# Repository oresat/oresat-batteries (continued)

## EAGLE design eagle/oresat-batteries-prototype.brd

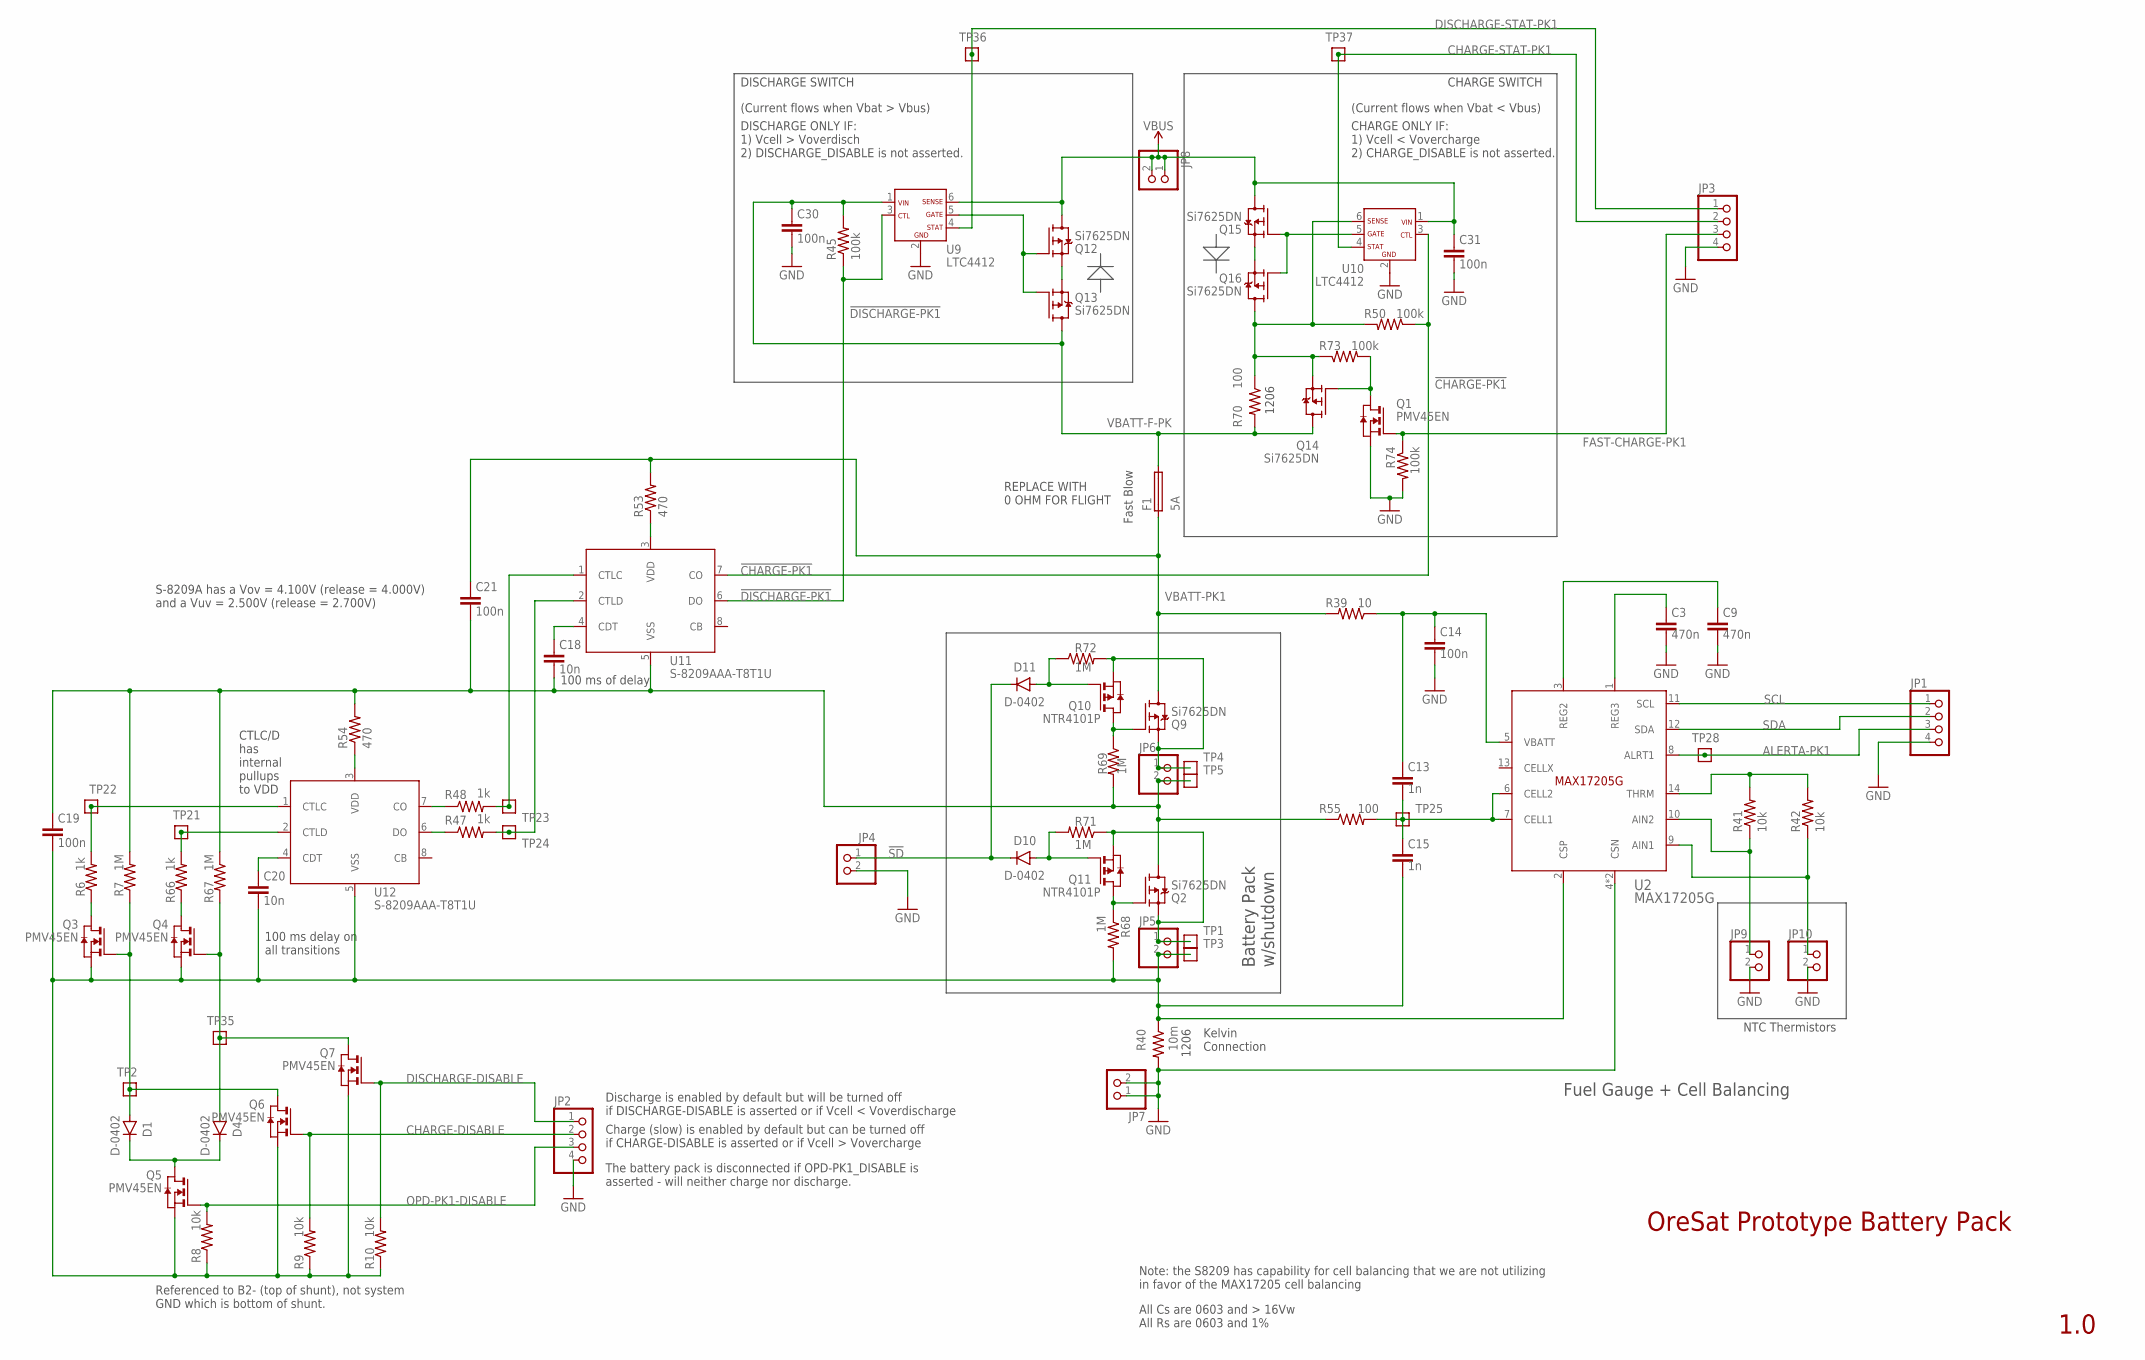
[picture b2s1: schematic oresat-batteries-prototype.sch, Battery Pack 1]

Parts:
C3, C9: 470n; .0603-C-NOSILK
C13, C15: 1n; .0603-C-NOSILK
C14, C19, C21, C30, C31: 100n; .0603-C-NOSILK
C18, C20: 10n; .0603-C-NOSILK
D1, D4, D10, D11: D-0402; .0402-B-NOSILK-DIODE; MPN 1N4148WL2-TP
F1: 5A; C0603; MPN ERB-RE5R00V
JP1, JP2, JP3: PINHD-1X4; 1X04
JP4, JP5, JP6, JP7, JP8, JP9, JP10: PINHD-1X2; 1X02
Q1, Q3, Q4, Q5, Q6, Q7: PMV45EN; SOT23; MPN DMG2302UK-7
Q2, Q9, Q12, Q13, Q14, Q15, Q16: Si7625DN; POWERPAK-1212-8; MPN SI7625DN-T1-GE3
Q10, Q11: NTR4101P; SOT23; MPN DMG3401LSN-7
R6, R47, R48, R66: 1k; .0603-C-NOSILK
R7, R67, R68, R69, R71, R72: 1M; .0603-C-NOSILK
R8, R9, R10, R41, R42: 10k; .0603-C-NOSILK
R39: 10; .0603-C-NOSILK
R40: 10m; 1206-C
R45, R50, R73, R74: 100k; .0603-C-NOSILK
R53, R54: 470; .0603-C-NOSILK
R55: 100; .0603-C-NOSILK
R70: 100; 1206-C
TP1, TP2, TP3, TP4, TP5, TP21, TP22, TP23, TP24, TP25, TP28, TP35, TP36, TP37: TEST-POINT; 2MM-TEST-POINT
U2: MAX17205G; 21-0137I_T1433-2; MPN MAX17205G+T
U9, U10: LTC4412; SOT23-6; MPN LTC4412HS6#TRMPBF
U11, U12: S-8209AAA-T8T1U; TSSOP8; MPN S-8209AAA-T8T1U

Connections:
!CHARGE-PK1: R50.1, U10.3 (CTL), U11.7 (CO)
!DISCHARGE-PK1: R45.1, U9.3 (CTL), U11.6 (DO)
!FAST-CHARGE-PK1: Q1.3 (D), Q14.4 (G), R73.2
!SD: D10.C, D11.C, JP4.1
AIN1-PK1: JP10.1, R42.1, U2.9 (AIN1)
AIN2-PK1: JP9.1, R41.1, U2.10 (AIN2)
ALERTA-PK1: JP1.3, TP28.1, U2.8 (ALRT1)
CELL1-PK1: C13.2, C15.1, R55.2, TP25.1, U2.6 (CELL2), U2.7 (CELL1)
CHARGE-DISABLE: JP2.2, Q6.1 (G), R9.2
CHARGE-STAT-PK1: JP3.2, TP37.1, U10.4 (STAT)
CSP-PK1: C15.2, C19.2, C20.2, JP5.2, Q3.2 (S), Q4.2 (S), Q5.2 (S), Q6.2 (S), Q7.2 (S), R8.1, R9.1, R10.1, R40.1, R68.2, TP3.1, U2.2 (CSP), U12.5 (VSS)
DISCHARGE-DISABLE: JP2.1, Q7.1 (G), R10.2
DISCHARGE-STAT-PK1: JP3.1, TP36.1, U9.4 (STAT)
FAST-CHARGE-PK1: JP3.3, Q1.1 (G), R74.1
GND: C3.2, C9.2, C14.2, C30.2, C31.2, JP1.4, JP2.4, JP3.4, JP4.2, JP7.1, JP7.2, JP9.2, JP10.2, Q1.2 (S), R40.2, R74.2, U2.4 (CSN), U2.EP (CSN), U9.2 (GND), U10.2 (GND)
unnamed: D1.C, D4.C, Q5.3 (D)
unnamed: R47.2, TP24.1, U11.2 (CTLD)
unnamed: R47.1, U12.6 (DO)
unnamed: R48.2, TP23.1, U11.1 (CTLC)
unnamed: Q4.3 (D), R66.1
unnamed: R48.1, U12.7 (CO)
unnamed: C20.1, U12.4 (CDT)
unnamed: Q12.4 (G), Q13.4 (G), U9.5 (GATE)
unnamed: Q12.1 (S), Q12.2 (S), Q12.3 (S), Q13.1 (S), Q13.2 (S), Q13.3 (S)
unnamed: Q3.3 (D), R6.1
unnamed: D4.A, Q4.1 (G), Q7.3 (D), R67.2, TP35.1
unnamed: C18.1, U11.4 (CDT)
unnamed: R6.2, TP22.1, U12.1 (CTLC)
unnamed: Q9.4 (G), Q10.3 (D), R69.1
unnamed: R53.1, U11.3 (VDD)
unnamed: R54.1, U12.3 (VDD)
unnamed: R66.2, TP21.1, U12.2 (CTLD)
unnamed: D10.A, Q11.1 (G), R71.2
unnamed: Q14.1 (S), Q14.2 (S), Q14.3 (S), Q16.5 (D), Q16.6 (D), Q16.7 (D), Q16.8 (D), Q16.PAD (D), R50.2, R70.1, R73.1, U10.6 (SENSE)
unnamed: JP6.1, Q9.1 (S), Q9.2 (S), Q9.3 (S), Q10.2 (S), R72.2, TP4.1
unnamed: Q15.4 (G), Q16.4 (G), U10.5 (GATE)
unnamed: Q15.1 (S), Q15.2 (S), Q15.3 (S), Q16.1 (S), Q16.2 (S), Q16.3 (S)
unnamed: Q2.4 (G), Q11.3 (D), R68.1
unnamed: D11.A, Q10.1 (G), R72.1
unnamed: D1.A, Q3.1 (G), Q6.3 (D), R7.1, TP2.1
unnamed: JP5.1, Q2.1 (S), Q2.2 (S), Q2.3 (S), Q11.2 (S), R71.1, TP1.1
unnamed: C18.2, C19.1, C21.2, JP6.2, Q2.5 (D), Q2.6 (D), Q2.7 (D), Q2.8 (D), Q2.PAD (D), R7.2, R54.2, R55.1, R67.1, R69.2, TP5.1, U11.5 (VSS)
OPD-PK1-DISABLE: JP2.3, Q5.1 (G), R8.2
REG2-PK1: C9.1, U2.3 (REG2)
REG3-PK1: C3.1, U2.1 (REG3)
SCL: JP1.1, U2.11 (SCL)
SDA: JP1.2, U2.12 (SDA)
THRM-PK1: R41.2, R42.2, U2.14 (THRM)
VBATT-F-PK: C30.1, F1.2, Q13.5 (D), Q13.6 (D), Q13.7 (D), Q13.8 (D), Q13.PAD (D), Q14.5 (D), Q14.6 (D), Q14.7 (D), Q14.8 (D), Q14.PAD (D), R45.2, R70.2, U9.1 (VIN)
VBATT-PK1: C21.1, F1.1, Q9.5 (D), Q9.6 (D), Q9.7 (D), Q9.8 (D), Q9.PAD (D), R39.2, R53.2
VBATT-PL1: C13.1, C14.1, R39.1, U2.5 (VBATT)
VBUS: C31.1, JP8.1, JP8.2, Q12.5 (D), Q12.6 (D), Q12.7 (D), Q12.8 (D), Q12.PAD (D), Q15.5 (D), Q15.6 (D), Q15.7 (D), Q15.8 (D), Q15.PAD (D), U9.6 (SENSE), U10.1 (VIN)

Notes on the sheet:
1206
NTC Thermistors
Battery Pack w/shutdown
Fuel Gauge + Cell Balancing
Note: the S8209 has capability for cell balancing that we are not utilizing in favor of the MAX17205 cell balancing
100 ms of delay
Fast Blow
DISCHARGE SWITCH
REPLACE WITH 0 OHM FOR FLIGHT
(Current flows when Vbat > Vbus)
DISCHARGE ONLY IF: 1) Vcell > Voverdisch 2) DISCHARGE_DISABLE is not asserted.
CTLC/D has internal pullups to VDD
100 ms delay on all transitions
Discharge is enabled by default but will be turned off if DISCHARGE-DISABLE is asserted or if Vcell < Voverdischarge
Charge (slow) is enabled by default but can be turned off if CHARGE-DISABLE is asserted or if Vcell > Vovercharge
CHARGE SWITCH
(Current flows when Vbat < Vbus)
CHARGE ONLY IF: 1) Vcell < Vovercharge 2) CHARGE_DISABLE is not asserted.
OreSat Prototype Battery Pack
1.0
Kelvin Connection
S-8209A has a Vov = 4.100V (release = 4.000V) and a Vuv = 2.500V (release = 2.700V)
Referenced to B2- (top of shunt), not system GND which is bottom of shunt.
The battery pack is disconnected if OPD-PK1_DISABLE is asserted - will neither charge nor discharge.
All Cs are 0603 and > 16Vw All Rs are 0603 and 1%

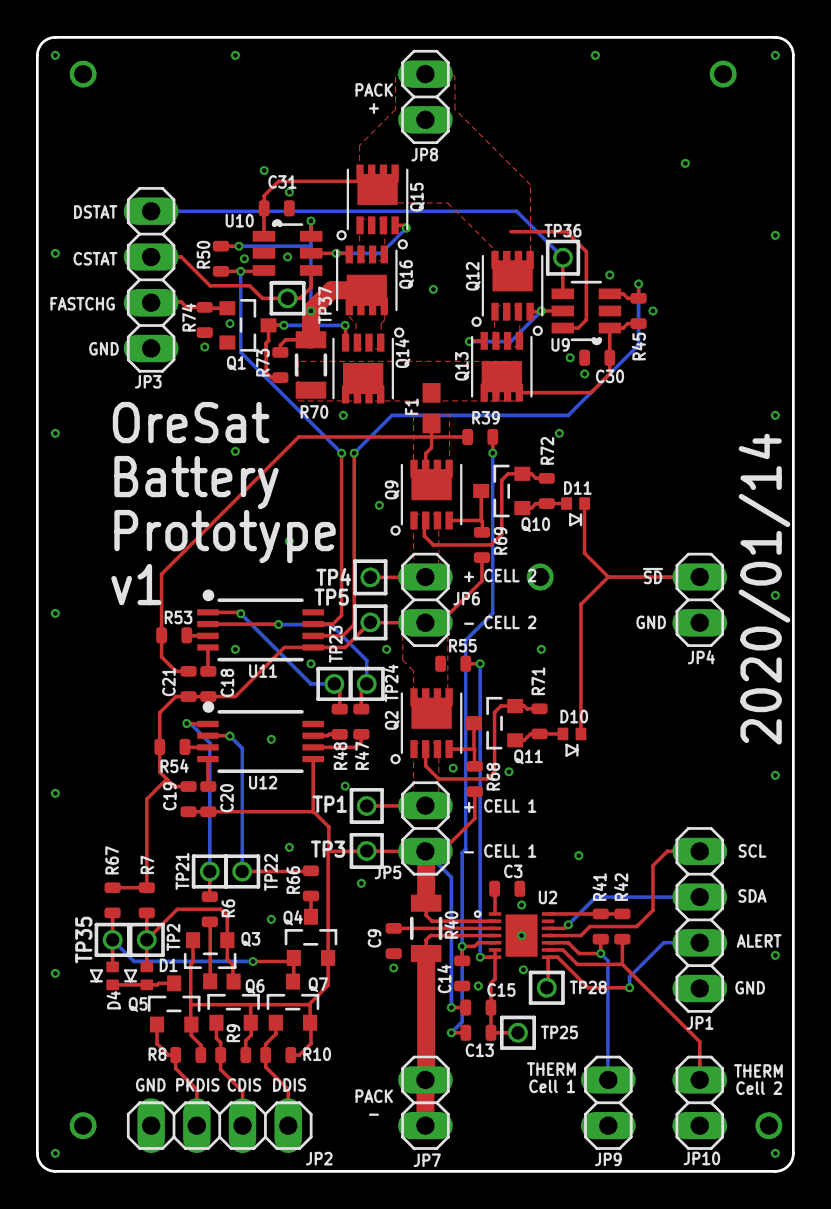
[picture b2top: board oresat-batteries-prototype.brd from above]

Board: 2 copper layers, 42.0 x 63.0 mm, 85 parts (0 on the bottom side), 52 nets.

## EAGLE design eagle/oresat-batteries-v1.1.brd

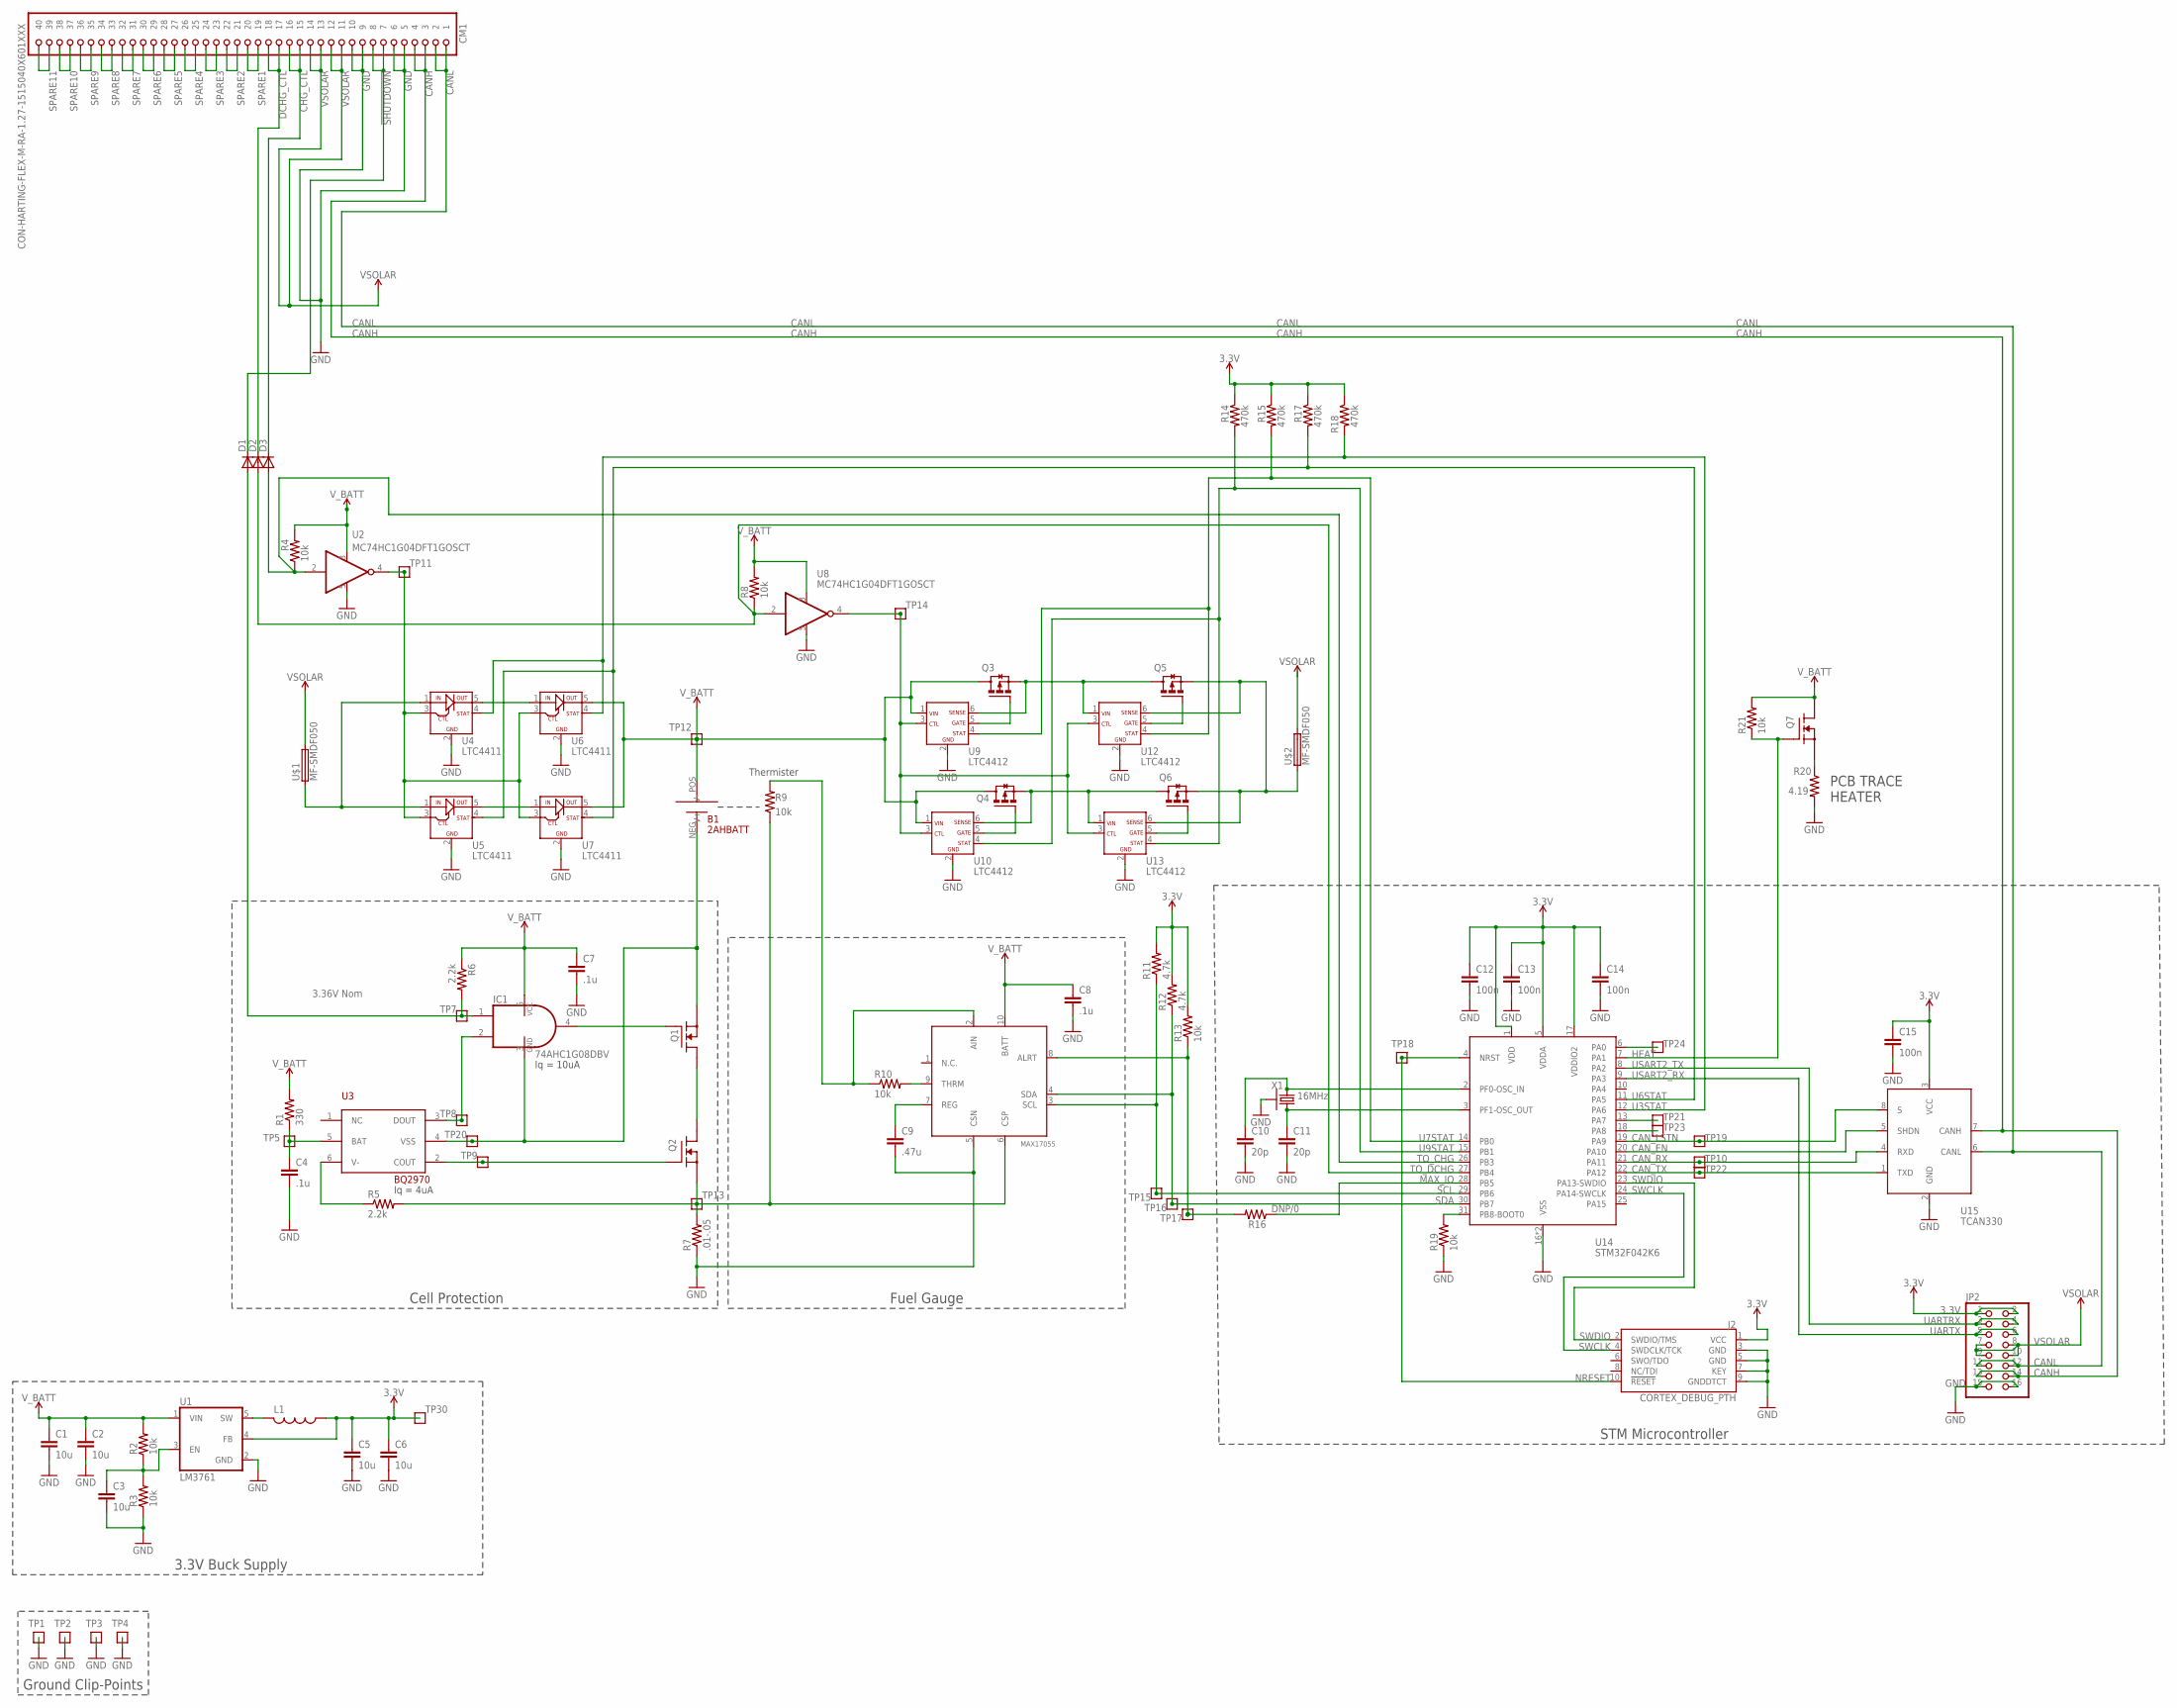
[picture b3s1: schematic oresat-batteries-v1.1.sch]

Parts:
B1: 2AHBATT; 2AH_605060
C1, C2, C3, C5, C6: 10u; C0805
C4, C7, C8: .1u; C0603
C9: .47u; C0603
C10, C11: 20p; C0603
C12, C13, C14, C15: 100n; C0603
CM1: CON-HARTING-FLEX-M-RA-1.27-1515040X601XXX; CON-1.27-M-RA-HARTING-1515040X601XXX
D1, D2, D3: CMDD6001; SOD323
IC1: 74AHC1G08DBV; SOT23-5
J2: CORTEX_DEBUG_PTH; 2X5-PTH-1.27MM
JP2: PINHD-2X8; 2X08
L1: L-USL2012C; L2012C
Q1, Q2, Q7: CSD16340Q3; Q3
Q3, Q4, Q5, Q6: TPN4R712MD; TSON-ADVANCE-3X3
R1: 330; R0603
R2, R3, R4, R8, R9, R10, R13, R19, R21: 10k; R0603
R5, R6: 2.2k; R0603
R7: .01-.05; R2512
R11, R12: 4.7k; R0603
R14, R15, R17, R18: 470k; R0603
R16: DNP/0; R0603
R20: 4.19; RES_HEATER
TP1, TP2, TP3, TP4, TP5, TP7, TP8, TP9, TP10, TP11, TP12, TP13, TP14, TP15, TP16, TP17, TP18, TP19, TP20, TP21, TP22, TP23, TP24, TP30: TP; 2MM_TP
U1: LM3761; SOT23-5
U2, U8: MC74HC1G04DFT1GOSCT; SC70-5
U3: BQ2970; PSOP6
U4, U5, U6, U7: LTC4411; SOT23-5-B
U9, U10, U12, U13: LTC4412; SOT23-6
U11: MAX17055; TDFN-10L
U14: STM32F042K6; QFP32-7X7
U15: TCAN330; SOT23-8_TI-DCN
U$1, U$2: MF-SMDF050
X1: 16MHz; CRYSTAL_2.5X2

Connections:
3.3V: C5.1, C6.1, C12.1, C13.1, C14.1, C15.1, J2.1 (VCC), JP2.1, JP2.2, L1.1, R11.2, R12.2, R13.2, R14.1, R15.1, R17.1, R18.1, TP30.P$1, U1.4 (FB), U14.1 (VDD), U14.5 (VDDA), U14.17 (VDDIO2), U15.3 (VCC)
4411MB: U5.5 (OUT), U7.1 (IN)
4411_MT: U4.5 (OUT), U6.1 (IN)
!SHUTDOWN: CM1.7, CM1.8, D1.1 (C)
ALERT: R13.1, R16.2, TP17.P$1, U11.8 (ALRT)
ANDDRIVE: IC1.4 (O), Q1.P$4 (G)
BATT-: B1.NEG (V-), IC1.3 (GND), Q1.P$1 (S), Q1.P$2 (S), Q1.P$3 (S), TP20.P$1, U3.4 (VSS)
BETSHUT: Q1.P$5 (D), Q1.P$6 (D), Q1.P$7 (D), Q1.P$8 (D), Q1.P$9 (D), Q2.P$5 (D), Q2.P$6 (D), Q2.P$7 (D), Q2.P$8 (D), Q2.P$9 (D)
BGDOUT: IC1.2 (I1), TP8.P$1, U3.3 (DOUT)
BQBAT: C4.1, R1.1, TP5.P$1, U3.5 (BAT)
BQCOUT: Q2.P$4 (G), TP9.P$1, U3.2 (COUT)
BQVMIN: R5.1, U3.6 (V-)
CANH: CM1.3, CM1.4, JP2.13, JP2.14, U15.7 (CANH)
CANL: CM1.1, CM1.2, JP2.11, JP2.12, U15.6 (CANL)
CAN_EN: U14.20 (PA10), U15.5 (SHDN)
CAN_LSTN: TP19.P$1, U14.19 (PA9), U15.8 (S)
CAN_RX: TP10.P$1, U14.21 (PA11), U15.4 (RXD)
CAN_TX: TP22.P$1, U14.22 (PA12), U15.1 (TXD)
CHG_CTL: CM1.15, CM1.16, D3.1 (C)
CHG_SHD: TP11.P$1, U2.4 (OUT), U4.3 (CTL), U5.3 (CTL), U6.3 (CTL), U7.3 (CTL)
C_SENSE: Q2.P$1 (S), Q2.P$2 (S), Q2.P$3 (S), R5.2, R7.2, R9.1, TP13.P$1, U11.6 (CSP)
DCHG_CTL: CM1.17, CM1.18, D2.1 (C)
DSCHG_SHD: TP14.P$1, U8.4 (OUT), U9.3 (CTL), U10.3 (CTL), U12.3 (CTL), U13.3 (CTL)
GND: C1.2, C2.2, C3.2, C4.2, C5.2, C6.2, C7.2, C8.2, C9.2, C10.2, C11.2, C12.2, C13.2, C14.2, C15.2, CM1.5, CM1.6, CM1.9, CM1.10, J2.3 (GND), J2.5 (GND), J2.7 (KEY), J2.9 (GNDDTCT), JP2.15, JP2.16, R3.1, R7.1, R19.1, R20.V- (2), TP1.P$1, TP2.P$1, TP3.P$1, TP4.P$1, U1.2 (GND), U2.5 (GND), U4.2 (GND), U5.2 (GND), U6.2 (GND), U7.2 (GND), U8.5 (GND), U9.2 (GND), U10.2 (GND), U11.5 (CSN), U12.2 (GND), U13.2 (GND), U14.16 (VSS), U14.32 (VSS), U15.2 (GND), X1.2 (SHIELD), X1.4 (SHIELD)
HEAT: Q7.P$4 (G), R21.1, U14.7 (PA1)
INFUSE: U4.1 (IN), U5.1 (IN), U$1.1
MAX_IO: R16.1, U14.28 (PB5)
unnamed: L1.2, U1.5 (SW)
unnamed: R19.2, U14.31 (PB8-BOOT0)
unnamed: TP23.P$1, U14.18 (PA8)
unnamed: C3.1, R2.1, R3.2, U1.3 (EN)
unnamed: Q5.4 (G), U12.5 (GATE)
unnamed: Q3.1 (S), Q3.2 (S), Q3.3 (S), Q5.5 (D), Q5.6 (D), Q5.7 (D), Q5.8 (D), U9.6 (SENSE), U12.1 (VIN)
unnamed: Q3.4 (G), U9.5 (GATE)
unnamed: Q7.P$1 (S), Q7.P$2 (S), Q7.P$3 (S), R20.V+ (1)
unnamed: TP24.P$1, U14.6 (PA0)
unnamed: Q6.4 (G), U13.5 (GATE)
unnamed: Q4.1 (S), Q4.2 (S), Q4.3 (S), Q6.5 (D), Q6.6 (D), Q6.7 (D), Q6.8 (D), U10.6 (SENSE), U13.1 (VIN)
unnamed: Q4.4 (G), U10.5 (GATE)
NRESET: J2.10 (!RESET), TP18.P$1, U14.4 (NRST)
OSC_IN: C10.1, U14.2 (PF0-OSC_IN), X1.1
OSC_OUT: C11.1, U14.3 (PF1-OSC_OUT), X1.3 (2)
OUTFUSE: Q5.1 (S), Q5.2 (S), Q5.3 (S), Q6.1 (S), Q6.2 (S), Q6.3 (S), U12.6 (SENSE), U13.6 (SENSE), U$2.1
REG: C9.1, U11.7 (REG)
SCL: R11.1, TP15.P$1, U11.3 (SCL), U14.29 (PB6)
SDA: R12.1, TP16.P$1, U11.4 (SDA), U14.30 (PB7)
SPARE1: CM1.19, CM1.20
SPARE2: CM1.21, CM1.22
SPARE3: CM1.23, CM1.24
SPARE4: CM1.25, CM1.26
SPARE5: CM1.27, CM1.28
SPARE6: CM1.29, CM1.30
SPARE7: CM1.31, CM1.32
SPARE8: CM1.33, CM1.34
SPARE9: CM1.35, CM1.36
SPARE10: CM1.37, CM1.38
SPARE11: CM1.39, CM1.40
SWCLK: J2.4 (SWDCLK/TCK), U14.24 (PA14-SWCLK)
SWDIO: J2.2 (SWDIO/TMS), U14.23 (PA13-SWDIO)
SYSSHD: D1.2 (A), IC1.1 (I0), R6.2, TP7.P$1
TEMPSENSE: R9.2, R10.1, U11.2 (AIN)
THRM: R10.2, U11.9 (THRM)
TO_CHG: D3.2 (A), R4.1, U2.2 (INA), U14.26 (PB3)
TO_DCHG: D2.2 (A), R8.1, U8.2 (INA), U14.27 (PB4)
TP21: TP21.P$1, U14.13 (PA7)
U3STAT: R18.2, U4.4 (STAT), U6.4 (STAT), U14.12 (PA6)
U6STAT: R17.2, U5.4 (STAT), U7.4 (STAT), U14.11 (PA5)
U7STAT: R15.2, U9.4 (STAT), U12.4 (STAT), U14.14 (PB0)
U9STAT: R14.2, U10.4 (STAT), U13.4 (STAT), U14.15 (PB1)
USART2_RX: JP2.5, JP2.6, U14.9 (PA3)
USART2_TX: JP2.3, JP2.4, U14.8 (PA2)
VSOLAR: CM1.11, CM1.12, CM1.13, CM1.14, JP2.7, JP2.8, JP2.9, JP2.10, U$1.2, U$2.2
V_BATT: B1.POS (V+), C1.1, C2.1, C7.1, C8.1, IC1.5 (VCC), Q3.5 (D), Q3.6 (D), Q3.7 (D), Q3.8 (D), Q4.5 (D), Q4.6 (D), Q4.7 (D), Q4.8 (D), Q7.P$5 (D), Q7.P$6 (D), Q7.P$7 (D), Q7.P$8 (D), Q7.P$9 (D), R1.2, R2.2, R4.2, R6.1, R8.2, R21.2, TP12.P$1, U1.1 (VIN), U2.3 (VCC), U6.5 (OUT), U7.5 (OUT), U8.3 (VCC), U9.1 (VIN), U10.1 (VIN), U11.10 (BATT)

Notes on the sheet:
SCL
SDA
USART2_TX
USART2_RX
CAN_LSTN
CAN_EN
CAN_RX
CAN_TX
SWDIO
SWCLK
UARTRX
UARTX
CANH
VSOLAR
CANL
GND
HEAT
3.36V Nom
Fuel Gauge
STM Microcontroller
Cell Protection
Thermister
Iq = 10uA
Iq = 4uA
PCB TRACE HEATER
3.3V Buck Supply
Ground Clip-Points

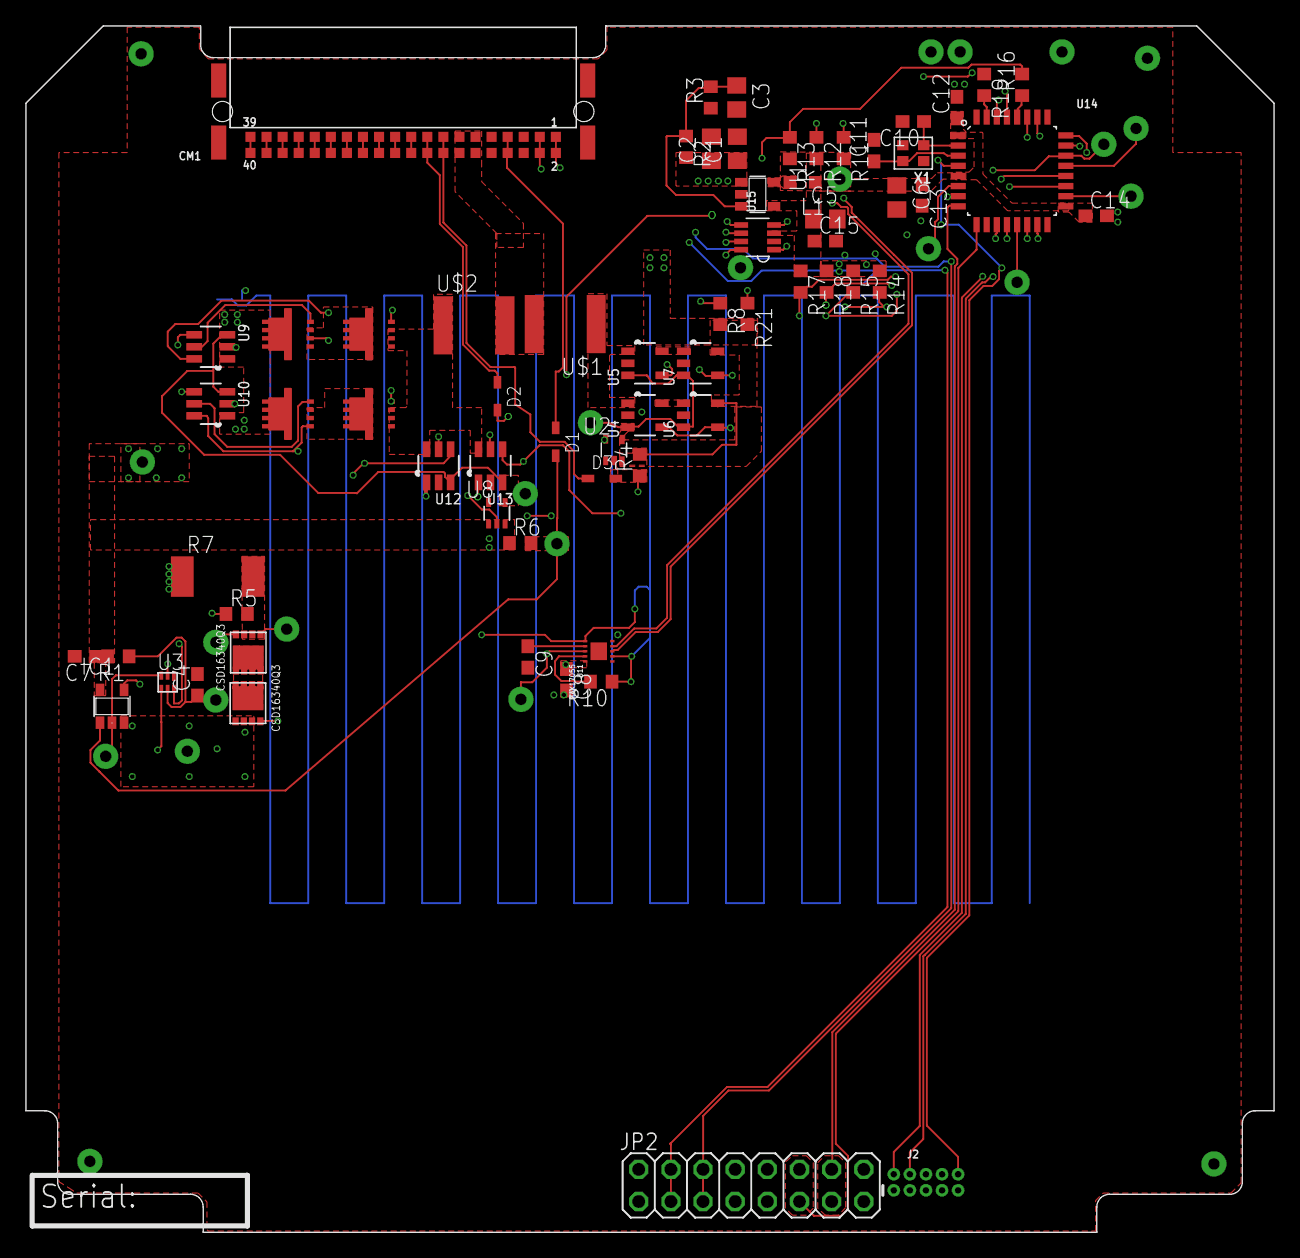
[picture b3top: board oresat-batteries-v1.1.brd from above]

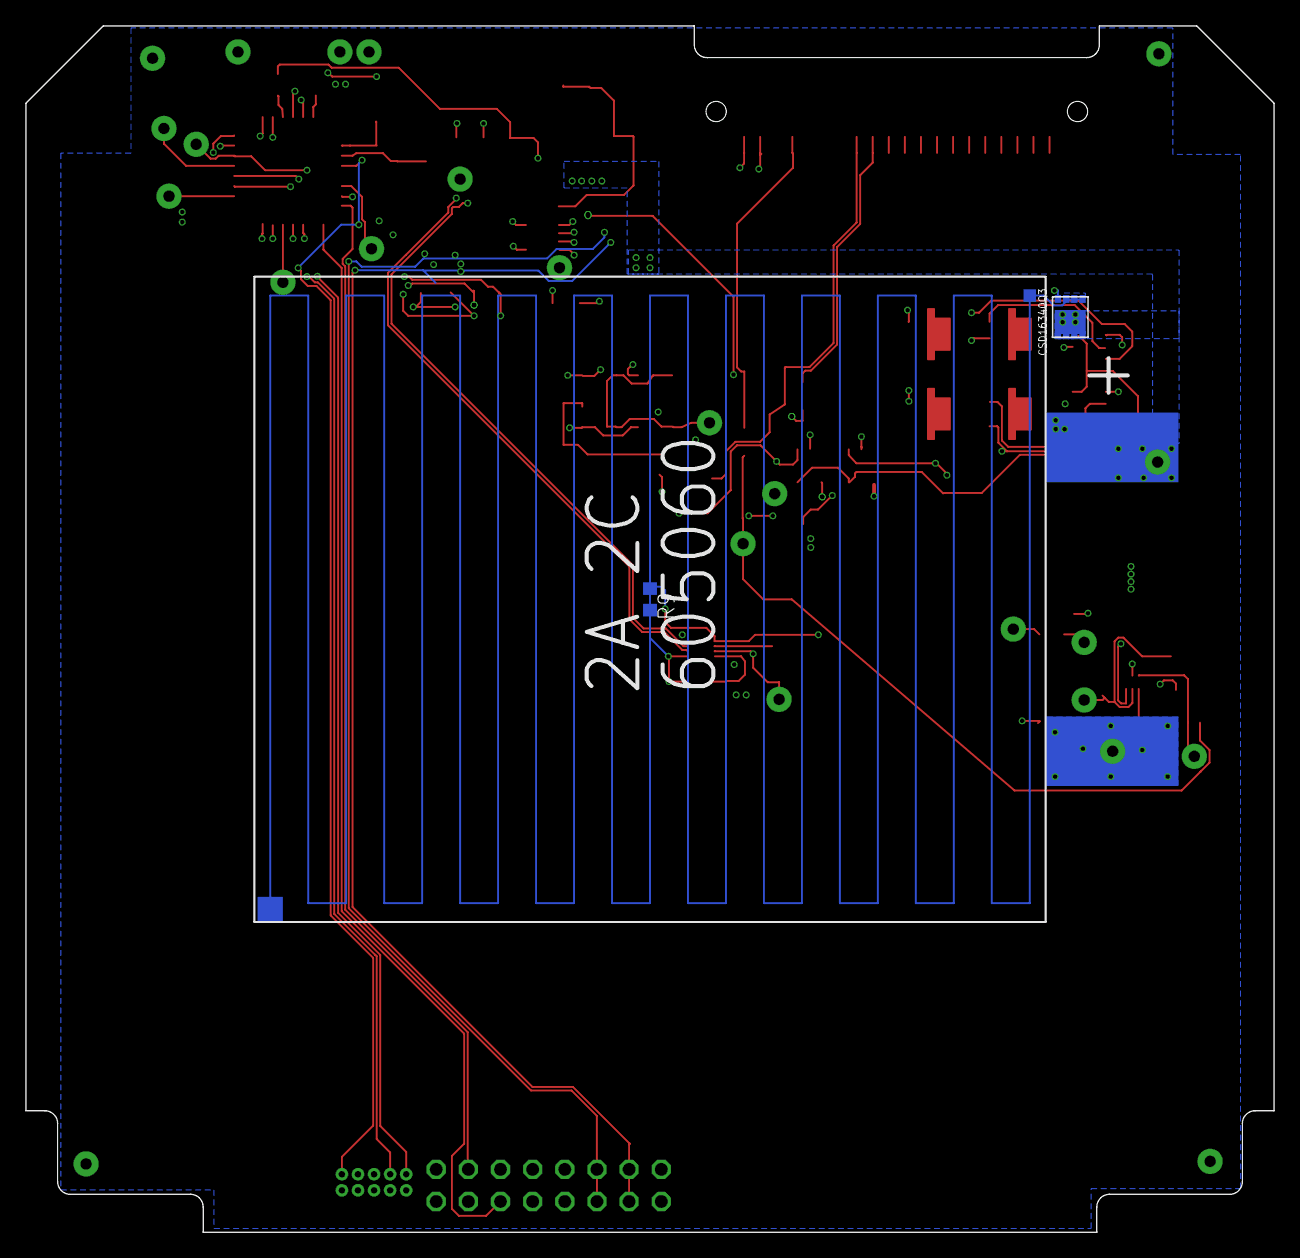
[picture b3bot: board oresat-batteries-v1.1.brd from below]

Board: 4 copper layers, 98.6 x 95.3 mm, 95 parts (4 on the bottom side), 73 nets.

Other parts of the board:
U$7: ORESAT-CARD-V0.5

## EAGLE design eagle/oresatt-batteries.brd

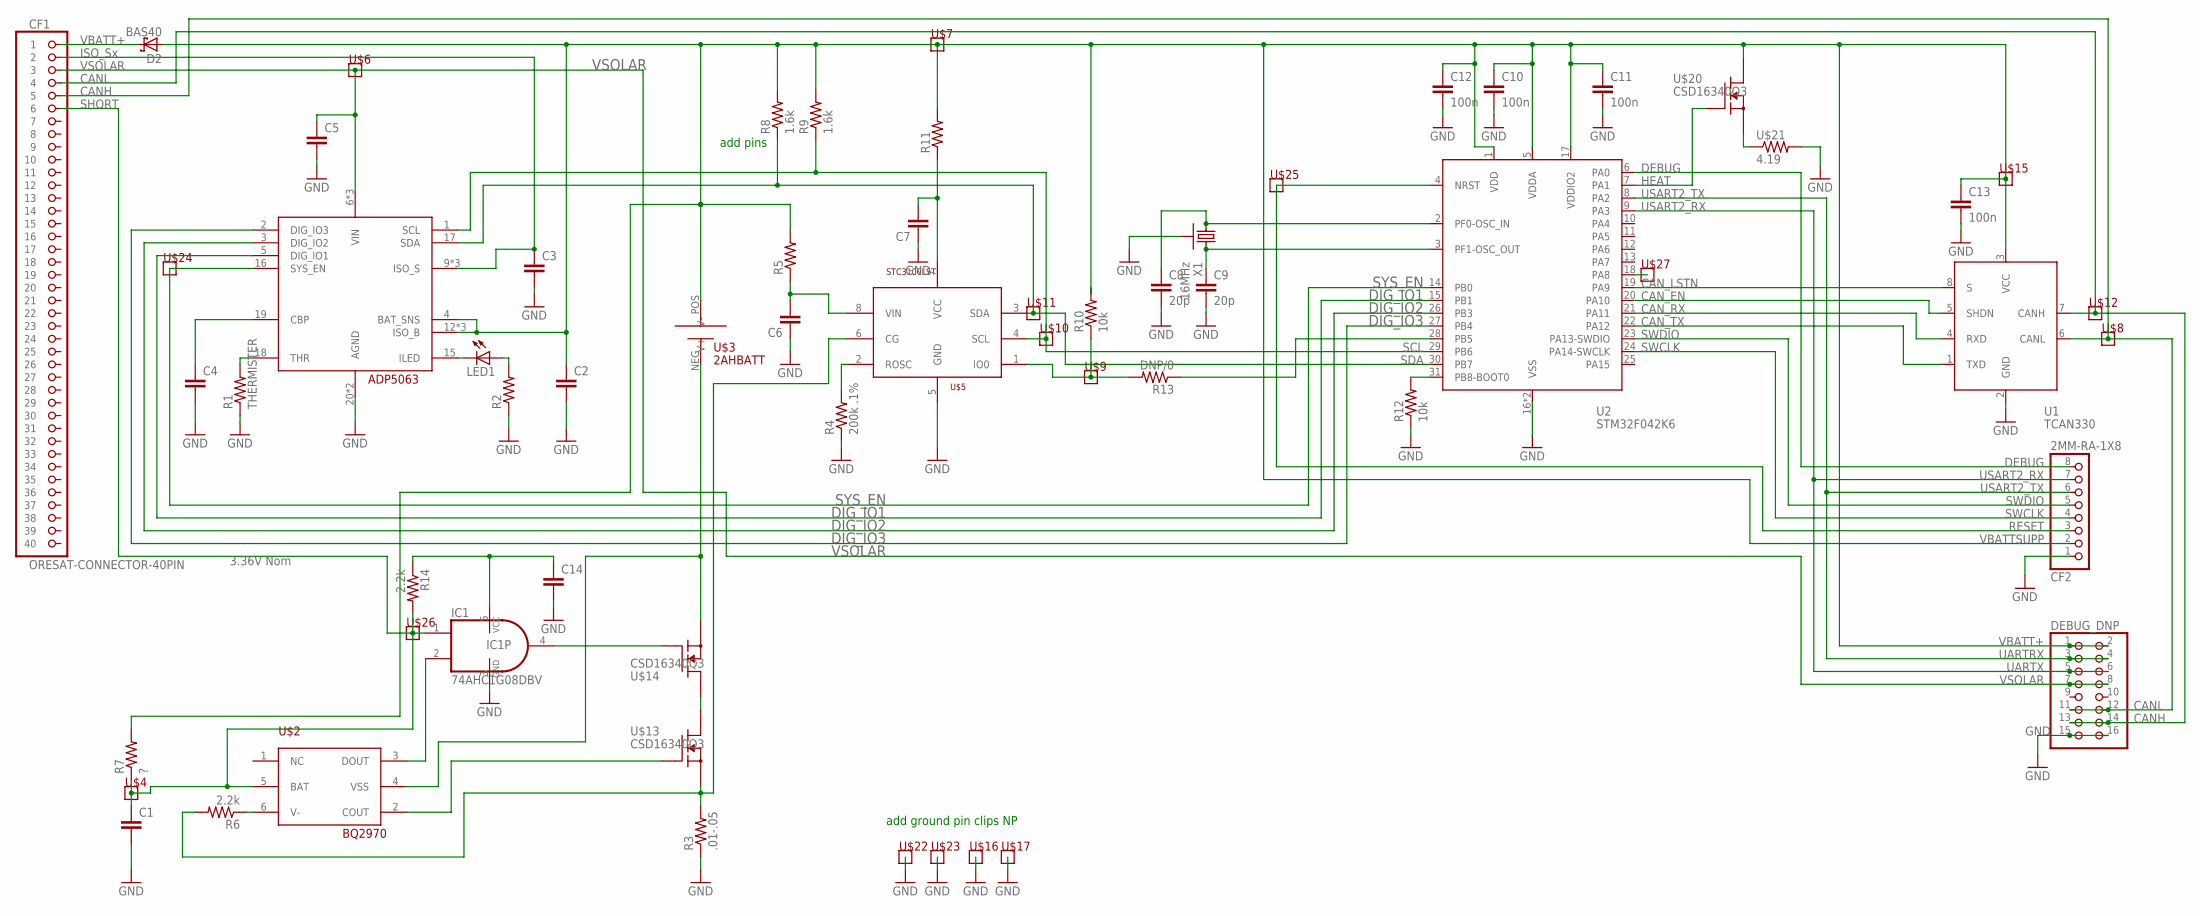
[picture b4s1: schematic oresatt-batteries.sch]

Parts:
C1, C2, C3, C4, C5, C6, C7, C14: C-EUC0603; C0603
C8, C9: 20p; C0603
C10, C11, C12, C13: 100n; C0603
CF1: ORESAT-CONNECTOR-40PIN; HARWIN-ARCHER-M50-3202045
CF2: 2MM-RA-1X8; CF-2MM-RA-1X8-PRECIDIP-831
D2: BAS40; SOT23
DEBUG_DNP: PINHD-2X8; 2X08
IC1: 74AHC1G08DBV; SOT23-5
LED1: LEDCHIPLED_0603; CHIPLED_0603
R1: THERMISTER; R0603
R2, R5, R11: R-US_R0603; R0603
R3: .01-.05; R0603
R4: 200k .1%; R0603
R6, R14: 2.2k; R0603
R7: ?; R0603
R8, R9: 1.6k; R0603
R10, R12: 10k; R0603
R13: DNP/0; R0603
U1: TCAN330; SOT23-8_TI-DCN
U2: STM32F042K6; QFP32-7X7
U$1: ADP5063; 20_4X4_VVTQ
U$2: BQ2970; PSOP6
U$3: 2AHBATT; 2AH_605060
U$4, U$6, U$7, U$8, U$9, U$10, U$11, U$12, U$15, U$16, U$17, U$22, U$23, U$24, U$25, U$26, U$27: TP; 2MM_TP
U$5: STC3100LST; MINISO-8
U$13, U$14, U$20: CSD16340Q3; Q3
U$21: 4.19; RES_HEATER
X1: 16MHz; CRYSTAL_2.5X2

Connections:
ADP_CBP: C4.1, U$1.19 (CBP)
ADP_LED: LED1.C, U$1.15 (ILED)
ADP_THR: R1.2, U$1.18 (THR)
ANDDRIVE: IC1.4 (O), U$14.P$4 (G)
BETSHUT: U$13.P$5 (D), U$13.P$6 (D), U$13.P$7 (D), U$13.P$8 (D), U$13.P$9 (D), U$14.P$5 (D), U$14.P$6 (D), U$14.P$7 (D), U$14.P$8 (D), U$14.P$9 (D)
BQBAT: C1.1, CF1.P$6 (6), IC1.1 (I0), R7.1, R14.2, U$2.5 (BAT)
BQVMIN: R6.1, U$2.6 (V-)
CANH: CF1.P$4 (4), DEBUG_DNP.13, DEBUG_DNP.14, U1.7 (CANH)
CANL: CF1.P$5 (5), DEBUG_DNP.11, DEBUG_DNP.12, U1.6 (CANL)
CAN_EN: U1.5 (SHDN), U2.20 (PA10)
CAN_LSTN: U1.8 (S), U2.19 (PA9)
CAN_RX: U1.4 (RXD), U2.21 (PA11)
CAN_TX: U1.1 (TXD), U2.22 (PA12)
COUT: U$2.2 (COUT), U$13.P$4 (G)
C_SENSE: R3.2, R6.2, U$5.6 (CG), U$13.P$1 (S), U$13.P$2 (S), U$13.P$3 (S)
DIG_IO1: U2.15 (PB1), U$1.5 (DIG_IO1)
DIG_IO2: U2.26 (PB3), U$1.3 (DIG_IO2)
DIG_IO3: U2.27 (PB4), U$1.2 (DIG_IO3)
GND: C1.2, C2.2, C3.2, C4.2, C5.2, C6.1, C7.1, C8.2, C9.2, C10.2, C11.2, C12.2, C13.2, C14.2, CF2.1, DEBUG_DNP.15, DEBUG_DNP.16, IC1.3 (GND), R1.1, R2.1, R3.1, R4.1, R12.1, U1.2 (GND), U2.16 (VSS), U2.32 (VSS), U$1.20 (AGND), U$1.P$1 (AGND), U$5.5 (GND), U$21.V- (2), X1.2 (SHIELD), X1.4 (SHIELD)
HEAT: U2.7 (PA1), U$20.P$4 (G)
IO0: R10.1, R13.2, U$5.1 (IO0)
ISO_S: C3.1, CF1.P$2 (2), U$1.9 (ISO_S), U$1.10 (ISO_S), U$1.11 (ISO_S)
LEDNP: LED1.A, R2.2
unnamed: C7.2, R11.1, U$5.7 (VCC)
unnamed: R12.2, U2.31 (PB8-BOOT0)
unnamed: CF1.P$1 (1), D2.3 (C)
unnamed: IC1.2 (I1), U$2.3 (DOUT)
unnamed: C14.1, IC1.5 (VCC), R14.1
unnamed: U$20.P$1 (S), U$20.P$2 (S), U$20.P$3 (S), U$21.V+ (1)
NRESET: CF2.3, U2.4 (NRST)
OSC_IN: C8.1, U2.2 (PF0-OSC_IN), X1.1
OSC_OUT: C9.1, U2.3 (PF1-OSC_OUT), X1.3 (2)
PA8: U2.18 (PA8)
ROSC: R4.2, U$5.2 (ROSC)
SCL: R9.1, U2.29 (PB6), U$1.1 (SCL), U$5.4 (SCL)
SDA: R8.1, U2.30 (PB7), U$1.17 (SDA), U$5.3 (SDA)
STC_CG: U$2.4 (VSS), U$3.NEG (V-), U$14.P$1 (S), U$14.P$2 (S), U$14.P$3 (S)
STC_IO: R13.1, U2.28 (PB5)
STC_VIN: C6.2, R5.1, U$5.8 (VIN)
STM_DEBUG: CF2.8, U2.6 (PA0)
SWCLK: CF2.4, U2.24 (PA14-SWCLK)
SWDIO: CF2.5, U2.23 (PA13-SWDIO)
SYS_EN: U2.14 (PB0), U$1.16 (SYS_EN)
USART2_RX: CF2.7, DEBUG_DNP.5, DEBUG_DNP.6, U2.9 (PA3)
USART2_TX: CF2.6, DEBUG_DNP.3, DEBUG_DNP.4, U2.8 (PA2)
VBATT+: C2.1, C10.1, C11.1, C12.1, C13.1, CF2.2, D2.1 (A), DEBUG_DNP.1, DEBUG_DNP.2, R5.2, R7.2, R8.2, R9.2, R11.2, U1.3 (VCC), U2.1 (VDD), U2.5 (VDDA), U2.17 (VDDIO2), U$1.4 (BAT_SNS), U$1.12 (ISO_B), U$1.13 (ISO_B), U$1.14 (ISO_B), U$3.POS (V+), U$20.P$5 (D), U$20.P$6 (D), U$20.P$7 (D), U$20.P$8 (D), U$20.P$9 (D)
VSOLAR: C5.1, CF1.P$3 (3), DEBUG_DNP.7, DEBUG_DNP.8, U$1.6 (VIN), U$1.7 (VIN), U$1.8 (VIN)

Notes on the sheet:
SCL
SDA
USART2_TX
USART2_RX
DEBUG
CAN_LSTN
CAN_EN
CAN_RX
CAN_TX
SWDIO
SWCLK
RESET
VSOLAR
add pins
add ground pin clips NP
UARTRX
VBATT+
UARTX
CANH
CANL
GND
VBATTSUPP
DIG_IO3
DIG_IO2
DIG_IO1
SYS_EN
HEAT
ISO_Sx
SHORT
3.36V Nom

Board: 2 copper layers, 62 parts (2 on the bottom side), 46 nets, no tracks yet.
